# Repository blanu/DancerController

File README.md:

The 2N7002 transistor is an N-channel Power MOSFET.

With an N-channel MSOFET, the current flows from the drain to the source.
The source should be connected to ground.
The drain should be connected to the load.
To turn it on, the gate voltage must be more positive than the source voltage.
An important consideration in a MOSFET is the voltage difference it can handle between the drain and the source.
For The 2N7002, the maximum voltage difference tolerated is 60V.
Radio key jack voltages vary, but 60V should be sufficient.

The gate threshold voltage is how much the gate needs to be above the source in order to turn on, which for the 2N7002 is 1-2.5V.
Since the source should be connected to ground at 0V, that means that the activation voltage is 1-2.5V.
Therefore, the MOSFET switch will be open with the gate voltage is 1-2.5V and closed when the voltage is less than 1V.
The maximum voltage of a 3.3V microcontroller is 3.3V, so a resistor is needed to lower max voltage to between 1 and 2.5V.
This is both for the safety of your MOSFET and so that you can use digital microcontroller output pins instead of the more
limited in number analog output pins. However, if analog output pins are available then you could make do with setting the voltage
to 50%, which on many Arduinos I have worked with would be around 512 as an analog output value. However, check the specs of your
specific Arduino to determine how to achieve an output voltage within the tolerated range.

A 10K pull-down resistor between gate and source is used to drain away stray capacitance from the user that could otherwise
trigger the gate spuriously. A pull-down resistor ensures that the gate is either high or low and not floating.

A 1K resistor between the microcontroller and the gate decreases the current to the gate, which also decreases the rise and
fall time. It is also required to have SOME resistor in order to get the gate to work because the gate acts as a capacitor.
Adding a resistor allows you to more easily calculate the current flowing to the gate and therefore the switching time. otheriwse,
only the parasitic resistance of the circuit is in play, which is unknown. Another reason to add a resistor is to reduce
oscillations that can make the on-off transistion rough.

A zener diode from ground to the gate pin protects from overvoltage on the pin.

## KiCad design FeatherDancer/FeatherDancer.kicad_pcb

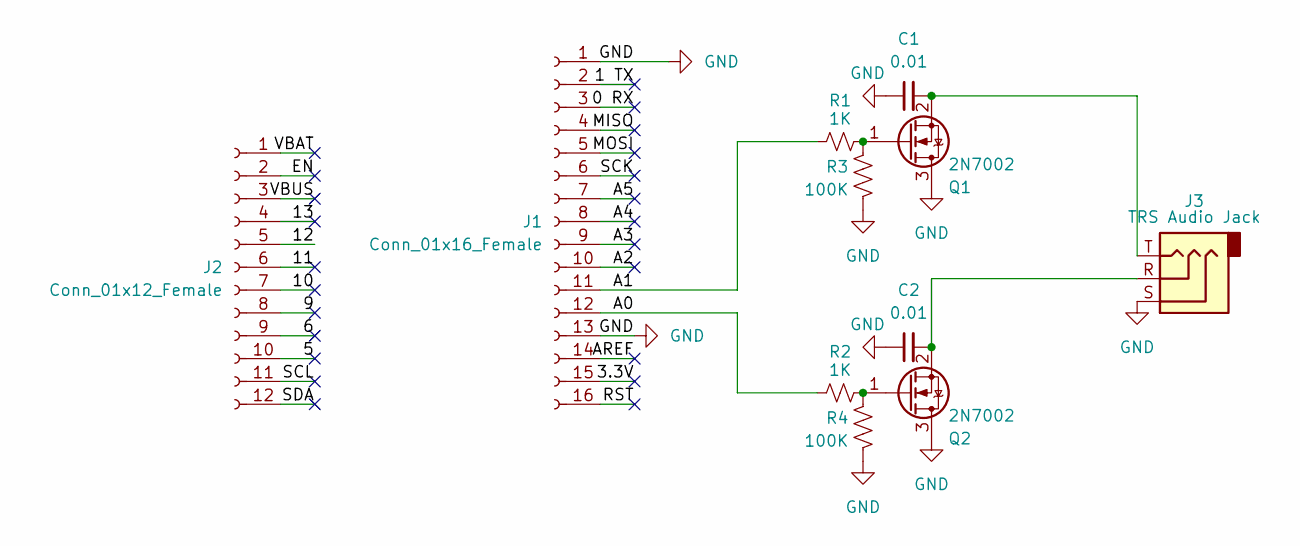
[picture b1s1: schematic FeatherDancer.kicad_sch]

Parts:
C1, C2: 0.01; C_Disc_D3.0mm_W1.6mm_P2.50mm
J1: Conn_01x16_Female; PinHeader_1x16_P2.54mm_Vertical
J2: Conn_01x12_Female; PinSocket_1x12_P2.54mm_Vertical
J3: TRS Audio Jack; Jack_3.5mm_CUI_SJ1-3533NG_Horizontal_CircularHoles
Q1, Q2: 2N7002; SOT-23
R1, R2: 1K; R_Axial_DIN0204_L3.6mm_D1.6mm_P5.08mm_Horizontal
R3, R4: 100K; R_Axial_DIN0204_L3.6mm_D1.6mm_P1.90mm_Vertical

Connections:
/0 RX: J1.3
/1 TX: J1.2
/3.3V: J1.15
/5: J2.10
/6: J2.9
/9: J2.8
/10: J2.7
/11: J2.6
/12: J2.5
/13: J2.4
/A0: J1.12, R2.2
/A1: J1.11, R1.2
/A2: J1.10
/A3: J1.9
/A4: J1.8
/A5: J1.7
/AREF: J1.14
/EN: J2.2
/MISO: J1.4
/MOSI: J1.5
/RST: J1.16
/SCK: J1.6
/SCL: J2.11
/SDA: J2.12
/VBAT: J2.1
/VBUS: J2.3
GND: C1.1, C2.1, J1.1, J1.13, J3.S, Q1.3 (D), Q2.3 (D), R3.2, R4.2
unnamed: Q1.1 (G), R1.1, R3.1
unnamed: C1.2, J3.T, Q1.2 (S)
unnamed: Q2.1 (G), R2.1, R4.1
unnamed: C2.2, J3.R, Q2.2 (S)

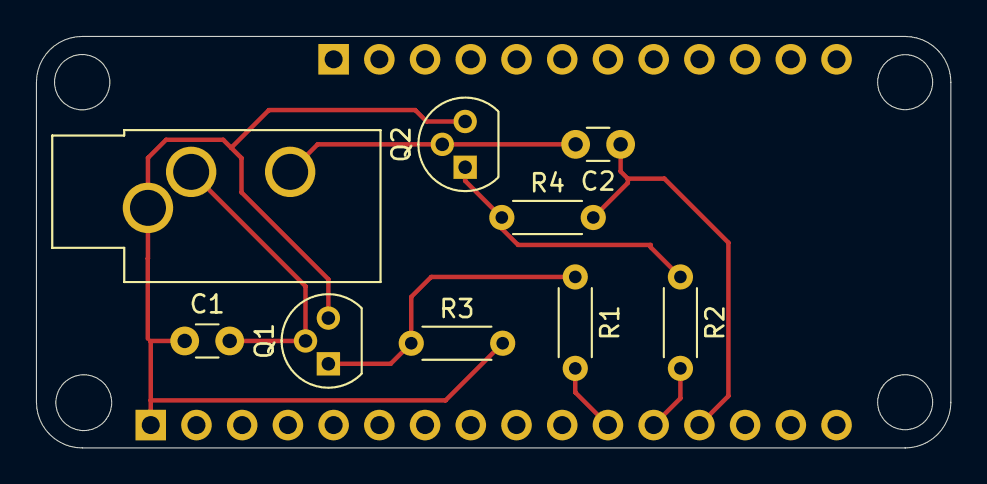
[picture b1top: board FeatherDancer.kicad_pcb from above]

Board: 2 copper layers, 50.8 x 22.9 mm, 11 parts (0 on the bottom side), 7 nets.

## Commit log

2024-09-04 Various updates
